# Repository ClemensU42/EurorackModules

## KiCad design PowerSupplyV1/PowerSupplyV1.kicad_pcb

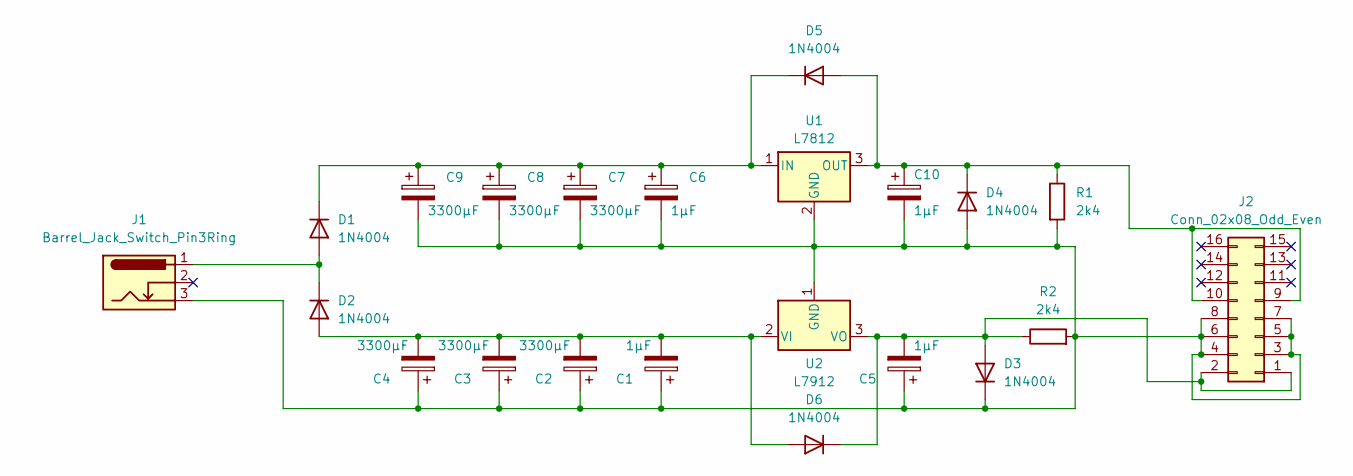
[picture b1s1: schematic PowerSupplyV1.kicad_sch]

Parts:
C1, C5, C6, C10: 1µF; CP_Radial_D12.5mm_P5.00mm
C2, C3, C4, C7, C8, C9: 3300µF; CP_Radial_D12.5mm_P5.00mm
D1, D2, D3, D4, D5, D6: 1N4004; D_DO-41_SOD81_P10.16mm_Horizontal
J1: Barrel_Jack_Switch_Pin3Ring; BarrelJack_Horizontal
J2: Conn_02x08_Odd_Even; IDC-Header_2x08_P2.54mm_Vertical
R1, R2: 2k4; R_Axial_DIN0204_L3.6mm_D1.6mm_P5.08mm_Horizontal
U1: L7812; TO-220F-3_Horizontal_TabDown
U2: L7912; TO-220F-3_Horizontal_TabDown

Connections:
unnamed: D1.2 (A), D2.1 (K), J1.1
unnamed: C6.1, C7.1, C8.1, C9.1, D1.1 (K), D5.1 (K), U1.1 (IN)
unnamed: C1.2, C2.2, C3.2, C4.2, D2.2 (A), D6.2 (A), U2.2 (VI)
unnamed: C5.2, D3.2 (A), D6.1 (K), J2.1, J2.2, R2.1, U2.3 (VO)
unnamed: C1.1, C2.1, C3.1, C4.1, C5.1, C6.2, C7.2, C8.2, C9.2, C10.2, D3.1 (K), D4.2 (A), J1.3, J2.3, J2.4, J2.5, J2.6, J2.7, J2.8, R1.2, R2.2, U1.2 (GND), U2.1 (GND)
unnamed: C10.1, D4.1 (K), D5.2 (A), J2.9, J2.10, R1.1, U1.3 (OUT)

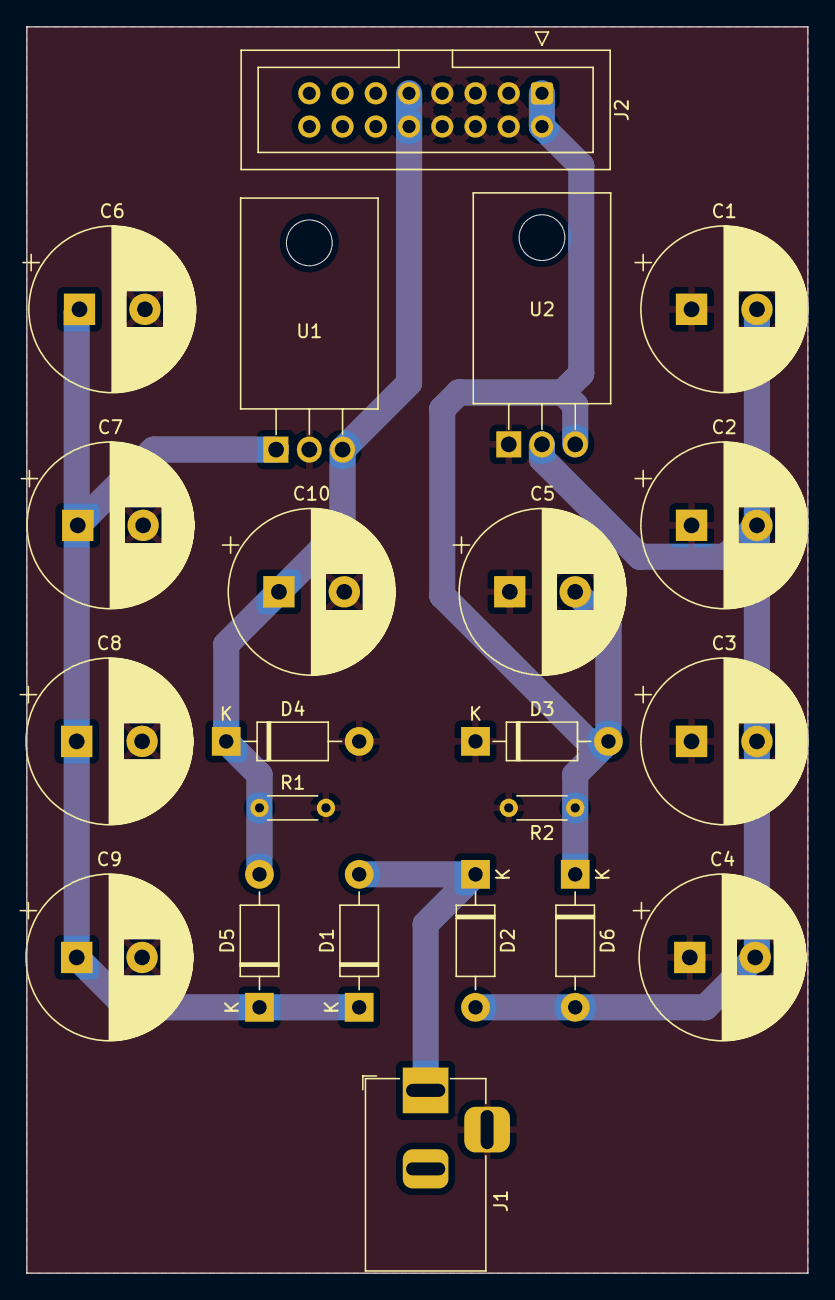
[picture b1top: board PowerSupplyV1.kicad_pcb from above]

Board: 2 copper layers, 59.7 x 95.2 mm, 22 parts (0 on the bottom side), 6 nets.

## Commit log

2024-06-21 created PowerSupplyV1 project
2024-06-21 created PowerSupplyV1 Schemativ and PCB Layout
2024-06-23 created ADSR Evelope Generator Project
2024-06-24 Added power connector, LM339 and TL074 IC to ADSREnvelope
